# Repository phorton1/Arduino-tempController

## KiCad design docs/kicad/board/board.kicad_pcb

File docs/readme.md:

# tempearature Controller

This is an ESP32 based Relay controller based on a **DS18B20** temperature
sensors.

## Please Also See

This project directly makes direct use of my
[**MyIOT**](https://github.com/phorton1/Arduino-libraries-myIOT)
("my internet of things*) repository, which provides a generalized approach to
building relatively simple parameter driven ESP32 devices that include a Web UI.

The PCBs (printed circuit boards) were **milled** using the
[**cnc3018**](https://github.com/phorton1/Arduino-esp32_cnc3018) CNC
machine that I built.

I hope you will take a few minutes to check out some of these other pages too!!

## Credits

This project directly relies upon the public open source Arduino development system,
the Espressif ESP32 online documentation and additions to the Arduino IDE, as
well as a number open source Arduino libraries

I would like to thank the countless individuals who have contributed to making these
development tools, source codes, and documentation available for free public use, including,
but not limited to:

- [KiCad](https://www.kicad.org/)
- [FlatCAM](https://bitbucket.org/jpcgt/flatcam/downloads/) by **Juan Pablo Caram**
- [Arduino IDE and Libraries](https://www.arduino.cc/)
- [Espressif Systems](https://www.espressif.com/en/products/socs/esp32)
- **jQuery**, **Bootstrap**, and the [jqPlot](Xhttp://www.jqplot.com/) javascript libraries

## License

This program, project, and repository is free software: you can redistribute it and/or modify
it under the terms of the GNU General Public License Version 3 as published by
the Free Software Foundation.

These materials are distributed in the hope that they will be useful,
but WITHOUT ANY WARRANTY; without even the implied warranty of
MERCHANTABILITY or FITNESS FOR ANY PARTICULAR PURPOSE.  See the
GNU General Public License for more details.

Please see [LICENSE.TXT](../LICENSE.TXT) for more information.

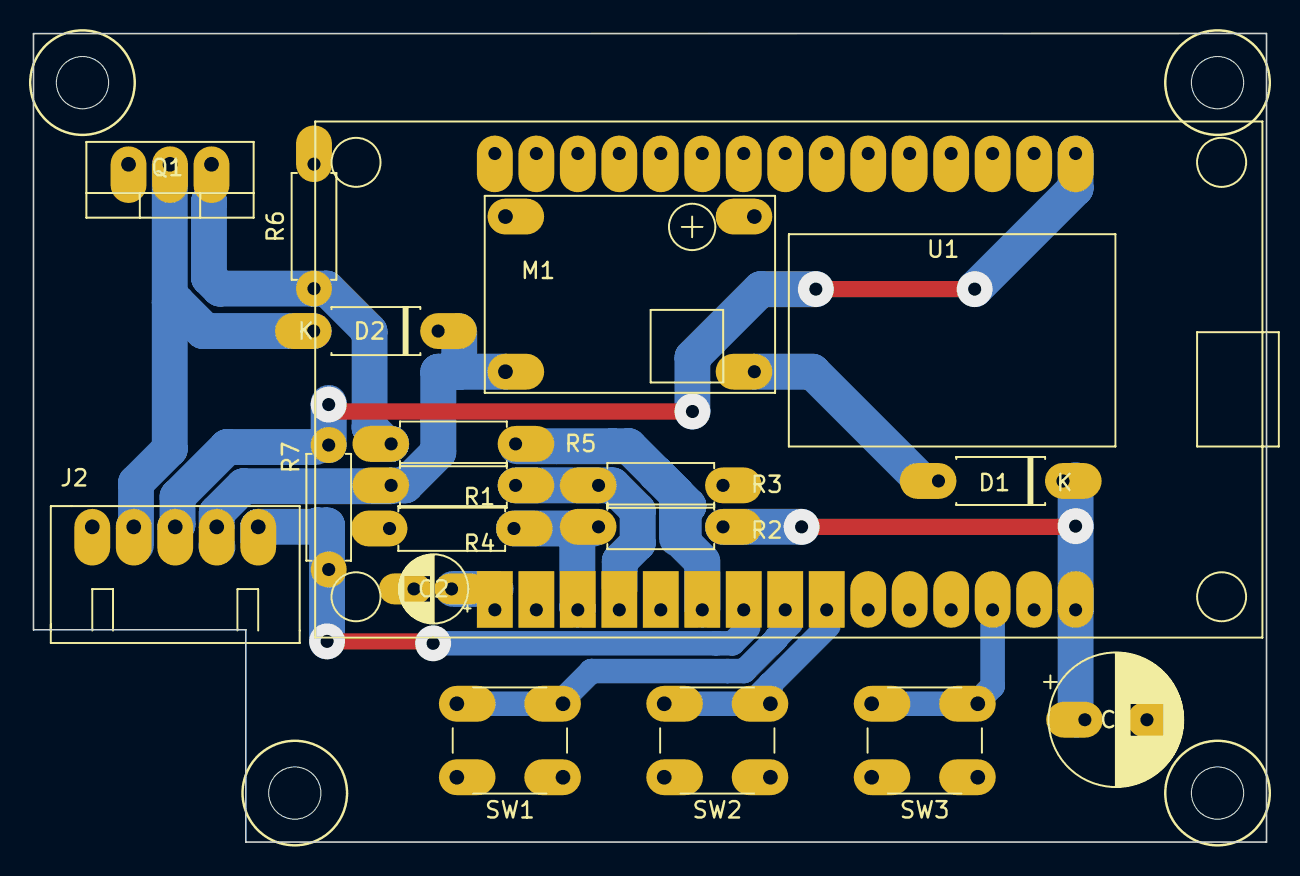
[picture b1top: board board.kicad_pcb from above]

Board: 2 copper layers, 75.5 x 49.5 mm, 18 parts (0 on the bottom side), 15 nets.

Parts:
C1: 100uf; CP_my100uf
C2: 4.7uf; CP_my10uf
D1: 1N4005; myDiodeSchotsky
D2: 1N5818; myDiodeSchotsky
J2: Connector; myJST5_right
M1: BUCK01; buck-mini360
Q1: IRLZ44N; myThreeLeggedDown
R1: 10K; resistor
R2, R4, R7: 4.7K; resistor
R3: 2K; resistor
R5: 100; resistor
R6: 10K; myResistor
SW1: BUTTON1; button_6mm_H8
SW2: BUTTON2; button_6mm_H8
SW3: BUTTON3; button_6mm_H8
U1: ESP32_DEV_0; esp32_oled_small

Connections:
+3V3: J2.3, R7.2, U1.30
+5V: C1.1, D1.1, R2.2, U1.1
+12V: D2.1, J2.4, M1.4, R1.2
BUTTON1: SW1.2, U1.8
BUTTON2: SW2.2, U1.7
BUTTON3: SW3.2, U1.3
EN: C2.1, U1.15
FAN-: D2.2, J2.2, Q1.2
GND: C1.2, C2.2, J2.1, M1.1, M1.2, Q1.3, R3.1, R4.1, R6.2, SW1.1, SW2.1, SW3.1, U1.2, U1.29
unnamed: D1.2, M1.3
unnamed: Q1.1, R5.2, R6.1
ONE_WIRE: J2.5, R7.1, U1.9
RELAY: R5.1, U1.10
S_5V: R2.1, R4.2, U1.13
S_12V: R1.1, R3.2, U1.12

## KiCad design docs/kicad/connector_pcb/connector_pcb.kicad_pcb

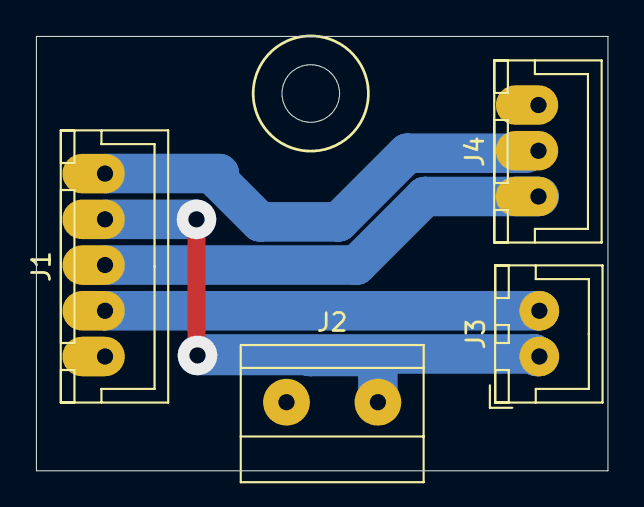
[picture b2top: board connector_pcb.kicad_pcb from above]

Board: 2 copper layers, 31.8 x 24.1 mm, 4 parts (0 on the bottom side), 5 nets.

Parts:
J1: Connector; JST5
J2: POWER; myTerminalBlock_5.08x02
J3: FAN; myJSTx02
J4: TEMP; JST3

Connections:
+3V3: J1.3, J4.1
+12V: J1.4, J2.2, J3.1
FAN-: J1.2, J3.2
GND: J1.1, J2.1, J4.3
ONE_WIRE: J1.5, J4.2

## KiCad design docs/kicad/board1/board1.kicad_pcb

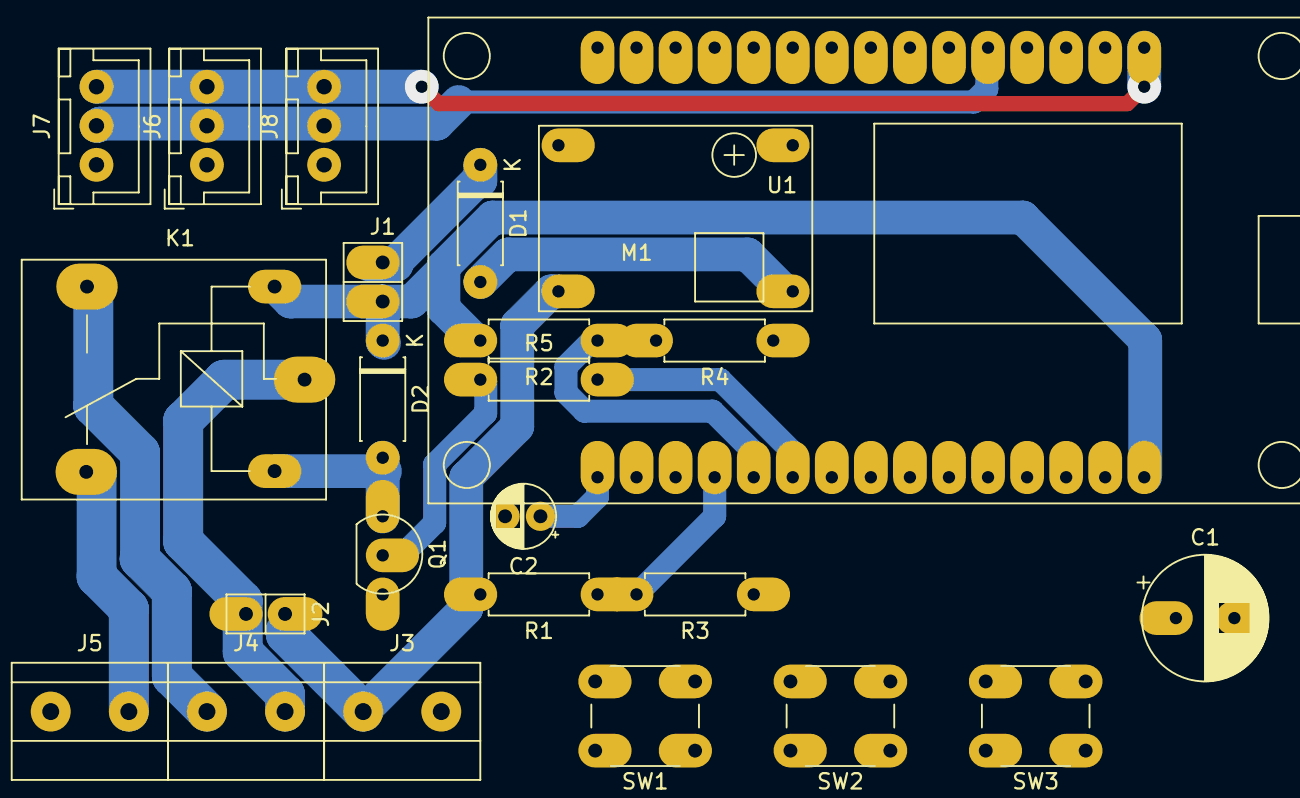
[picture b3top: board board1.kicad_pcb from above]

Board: 2 copper layers, 24 parts (0 on the bottom side), 19 nets.

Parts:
C1: 100uf; CP_my100uf
C2: 4.7uf; CP_my10uf
D1, D2: 1N400x; myDiodeSchotsky
J1: 5V_JUMP; pinHeader1x2
J2: 12V; myPinHeader_1x02
J3: POWER; myTerminalBlock_5.08x02
J4: RELAY; myTerminalBlock_5.08x02
J5: DEVICE; myTerminalBlock_5.08x02
J6, J7, J8: Temp; myJSTx03
K1: myRelay; myRelay2
M1: BUCK01; buck-mini360
Q1: BCS547; transistor
R1, R2: 10K; resistor
R3: 2K; resistor
R4: 4.7K; resistor
R5: 1K; resistor
SW1: BUTTON1; button_6mm_H12
SW2: BUTTON2; button_6mm_H12
SW3: BUTTON3; button_6mm_H12
U1: ESP32_DEV_0; esp32_oled_small

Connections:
+3V3: J6.3, J7.3, J8.3, U1.30
+5V: C1.1, D2.1, J1.2, K1.2, R2.2, U1.1
+12V: J2.1, J3.1, M1.4, R1.2
BUTTON1: SW1.2, U1.5
BUTTON2: SW2.2, U1.4
BUTTON3: SW3.2, U1.3
COMMON: J2.2, J4.2, K1.3
GND: C1.2, C2.2, J3.2, J5.1, J6.1, J7.1, J8.1, M1.1, M1.2, Q1.3, R3.1, R4.1, SW1.1, SW2.1, SW3.1, U1.2, U1.29
NC: J5.2, K1.4
NO: J4.1, K1.5
unnamed: C2.1, U1.15
unnamed: D1.1, J1.1
unnamed: D1.2, M1.3
unnamed: D2.2, K1.1, Q1.1
unnamed: Q1.2, R5.1
ONE_WIRE: J6.2, J7.2, J8.2, U1.26
RELAY: R5.2, U1.10
S_5V: R2.1, R4.2, U1.11
S_12V: R1.1, R3.2, U1.12

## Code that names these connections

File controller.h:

//----------------------------------------------
// constants for temperature controller
//----------------------------------------------
// Embedded SSD1306 display uses ESP32 standard I2C scl(22) sda(21)

#pragma once

#include <myIOTDevice.h>

#define WITH_ONBOARD_LED	1
	// shows blue if !wifi STATION


//=========================================================
// pins
//=========================================================

#define PIN_ONBOARD_LED		2
#define PIN_ONE_WIRE		33		// One-Wire bus to DS18B20 temperature probes

#define PIN_BUTTON1			25
#define PIN_BUTTON2			26
#define PIN_BUTTON3			13

#define PIN_S_12V			34		// sense 12V
#define PIN_S_5V			39		// sense buck 5V power supply

#define PIN_RELAY			32		// Actually, a MOSFET turns FAN on


//------------------------
// myIOT definition
//------------------------

#define TEMP_CONTROLLER			"tempController"
#define TEMP_CONTROLLER_VERSION	"tc0.1"
#define TEMP_CONTROLLER_URL		"https://github.com/phorton1/Arduino-boat-tempController"

#define BACKLIGHT_ALWAYS_ON			120

#define MIN_SETPOINT_DIF	2.0		// centigrade


#define TEMP_MODE_OFF			0
#define TEMP_MODE_ON_HIGH		1
#define TEMP_MODE_ON_LOW		2
#define TEMP_MODE_FORCE			3


#define ID_MODE						"MODE"
#define ID_SETPOINT_HIGH            "SETPOINT_HIGH"
#define ID_SETPOINT_LOW             "SETPOINT_LOW"
#define ID_TEMP_SENSE_ID            "TEMP_SENSE_ID"
#define ID_SENSE_SECS          		"SENSE_SECS"
#define ID_CALIB_VOLTS_12V          "CALIB_VOLTS_12V"
#define ID_CALIB_VOLTS_5V           "CALIB_VOLTS_5V"
#define ID_BACKLIGHT_SECS			"BACKLIGHT_SECS"

#define ID_STATUS					"STATUS"
#define ID_TEMPERATURE              "TEMPERATURE"
#define ID_RELAY_ON					"RELAY_ON"
#define ID_VOLTS_12V				"VOLTS_12V"
#define ID_VOLTS_5V					"VOLTS_5V"
#define ID_CHART_LINK				"CHART"



extern enumValue tempModes[];
	// in tempController.ino


class tempController : public myIOTDevice
{
public:

    tempController();
    ~tempController() {}

    virtual void setup() override;
    virtual void loop() override;

    // config values

	static int 		_mode;
	static float	_setpoint_high;
	static float	_setpoint_low;
	static String	_temp_sense_id;
	static int		_sense_secs;
	static float	_calib_volts_12v;
	static float	_calib_volts_5v;
	static int		_backlight_secs;

	// state values

	static String	_status_str;
	static float	_temperature;
	static bool		_relay_on;
	static float	_volts_12v;
	static float	_volts_5v;
	static String 	_chart_link;

	// public states available to other objects

	static int 		m_temp_error;	// low level error getting temperature

	// methods

	void setRelay(bool on);

	void stateMachine();
	static void stateTask(void *param);
	static void onSetPointChanged(const myIOTValue *value, float val);
	static void onBacklightChanged(const myIOTValue *value, int val);

	// extensions
	
	String onCustomLink(const String &path,  const char **mime_type) override;

};


extern tempController *controller;

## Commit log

2024-10-19 initial commit data submodule
2024-10-19 changed gitmodules manually
2024-10-19 revert .gitmodules change
2024-10-19 add Arduino-tempController to github
2024-10-19 submodule(data) auto_commit(c0e7ba5a) add better resizing to iotChart.js
2024-10-21 move generic uiButtons to myIOTButtons; implement initial tempController uiScreen and PCB board(s)
2024-10-21 submodule(data) auto_commit(b811e3f8) move generic uiButtons to myIOTButtons; implement initial tempController uiScreen and PCB board(s)
2024-10-22 initial build Controller PCB & Box - forgot ONE_WIRE pullup, changed to 100ohm RELAY resistor, temp removed fan flyback diode
2024-10-23 Power ideaSpark board via 3.3V line instead of VIN
2024-10-24 rework OLED UI; added Voltage sensing; comments and code prettiness
2024-10-24 normalized fridgeController to use myIOT Temperature sensor and Buttons; rename objects in fridgeController and tempController for consistency and name space separation.
2024-10-25 add tempController toolTips
2024-10-25 clear m_temp_error in WITH_FAKE_TEMPS
2024-10-25 reprint tempControllerBox top
2024-10-25 fix myIOTServer with new chart stuff (pass uuids, caching, etc)
2024-10-25 submodule(data) auto_commit(fdbad871) fix myIOTServer with new chart stuff (pass uuids, caching, etc)
2024-10-30 chnage Arduino-libraries-myIOT/myTempSensor to myIOTTempSensor to allow for a "my" version that is currently not on github
2024-12-11 design, print, and solder pcb_connector for Rhapsody tempController installation
2024-12-26 rebuild tempController box & pcb - back to 5V power supply
2024-12-26 back to 5V (DIN) buck power supply
2025-12-15 fixed minor typo (don't know how it compiled) in controller.cpp history circular buffer code
2025-12-15 submodule(data) auto_commit(b649fc3a) iotChart.js - added scheme for setting device specific series colors
2025-12-18 submodule(data) auto_commit(1adaeb45) reworked iotChart.js incremental update scheme starting with Arduino-boat-drainPump
2025-12-18 submodule(data) auto_commit(b6ac0c88) starting in Arduino-boat-arirco, major rework of iotChart.js and how charts are implemented - use common chart.html instead of specific/extra_data/device_chart.h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
2025-12-18 submodule(data) auto_commit(1efc7b72) rework iotChart.js::determineNumberTicks() starting with drain_pump
2025-12-18 submodule(data) auto_commit(78894e93) change onChartResize() to use create_chart() instead of built in jqplot.replot()
2025-12-18 submodule(data) auto_commit(40916b0c) separate iotChart.js doChart() as init only method from onXXX() UI methods - yet another rework of iotChart.js and myIOTDataLog starting with fridgeController
2025-12-18 back to static html for chart.html; got rid of myIOTDataLog::getChartHtml() starting with tempController
2025-12-18 commit Parent
2025-12-18 submodule(data) auto_commit(a4e2ed81) change chart.html and iotChart.js to use and remove style "degree_hidden" for devices that chart things with degrees
2025-12-18 submodule(data) auto_commit(a9754dbc) fixed renamed control _degree_type
2025-12-18 submodule(data) auto_commit(03555741) fix malformed chart.html <select id='_chart_period'> text
2025-12-19 submodule(data) auto_commit(1cb3d61a) add onChartResize() back to chart.html
2025-12-19 submodule(data) auto_commit(253976a9) more changes to iotChart.js starting with tempController so at least refresh works *well* if no zooming involved
2025-12-19 commit parents
2025-12-20 submodule(data) auto_commit(eccd1fcc) iotChart.js - added save/restore of series visibility and refactored code
2025-12-31 submodule(data) auto_commit(2a8db875) add degree_type to myIOT chart_header for use in initializing iotChart.js
2026-02-22 myIOTHTTP.cpp: added special case to do token replacement for "data_name" in chart.html AND updated myIOT devices with charts to pass data_name in chart_link
2026-02-22 submodule(data) auto_commit(37a6a76c) added framework for chart.html to pass "data_name" to allow multiple charts per device; ALSO store most recent chart period in browser storage
2026-03-04 added smaller (UINT8, CENTIGRADE8, UINT8x10) iotDataLog LOG_TYPES and updated client ctors
2026-03-04 submodule(data) auto_commit(75bcbcb5) iotChart.js - added smaller (UINT8, CENTIGRADE8, UINT8x10) iotDataLog LOG_TYPES and updated client ctors
2026-03-04 updated tempSensor to new LOG_COL_TYPE_CENTIGRADE32; log record *could* be shrunk and allow for many more in memory
2026-03-04 submodule(data) auto_commit(d6f02205) added myIotTempSensor "raw" accessors & used to shrink fridgeController.dataLog file size; got rid of FAKE_COMPRESSOR
2026-03-04 got rid of dubious ability to turn myIOT WIFI off and on
2026-03-05 added "boat" to the myIOTDevice advertised SSDP device URL
2026-03-05 remove forward and lateral references to myIOT "bilgeAlarm" repo
2026-03-05 submodule(data) auto_commit(ecc76888) update myIOT data submodule readme.md to remove forward references to actual implmented device repos
2026-03-07 submodule(data) auto_commit(5dbe3136) Save chart visibility and zorders in locsl storage
2026-06-28 submodule(data) auto_commit(eadab9ea) added myIOTDataLog type LOG_COL_TYPE_INT16_10 to support volts (fridgeController)
